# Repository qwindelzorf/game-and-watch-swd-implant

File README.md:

# Game & Watch SWD-Implant

A small [DAP-Link](https://github.com/ARMmbed/DAPLink) SWD programmer/debugger that fits insight a Nintendo® Game & Watch™ (2020/2021).

This is forked from [UlfWetzker/game-and-watch-swd-implant](https://github.com/UlfWetzker/game-and-watch-swd-implant), which has some issues and appears to be unmaintained.

## Mario (2020)

## Zelda (2021)

## Implant Firmware

The implant board itself uses a [SAMD21](https://www.microchip.com/en-us/product/atsamd21g18) microcontroller, which is flashed with the [DAP-Link](https://github.com/ARMmbed/DAPLink) firmware. It is then able to act as a flasher for the G&W [STM32](https://www.st.com/en/microcontrollers-microprocessors/stm32-32-bit-arm-cortex-mcus.html) CPU. Flashing both the implant and the G&W is done using [OpenOCD](https://openocd.org/).

## G&W Firmware

The go-to firmware for these consoles is "RetroGo":
- [Original](https://github.com/kbeckmann/game-and-watch-retro-go): archived now
- [Zeus Fork](https://github.com/olderzeus/game-and-watch-retro-go): Adds more consoles
- [Sylverb Fork](https://github.com/sylverb/game-and-watch-retro-go): Adds yet more consoles, as well as support for LttP and SMW.

## Other Links

- SD Card mod: [link](https://github.com/sylverb/game-and-watch-retro-go-sd)
- Original homebrew work: [link](https://github.com/ghidraninja/game-and-watch-backup)
- Various firmware and utilities: [link](https://www.schuerewegen.tk/gnw/)
- A good tutorial on modding & flashing: [link](https://psxtools.de/forum/index.php?thread/87820-tutorial-zelda-mario-game-and-watch-64mb-upgrade-dualboot-ofw-retro-go/) (German)

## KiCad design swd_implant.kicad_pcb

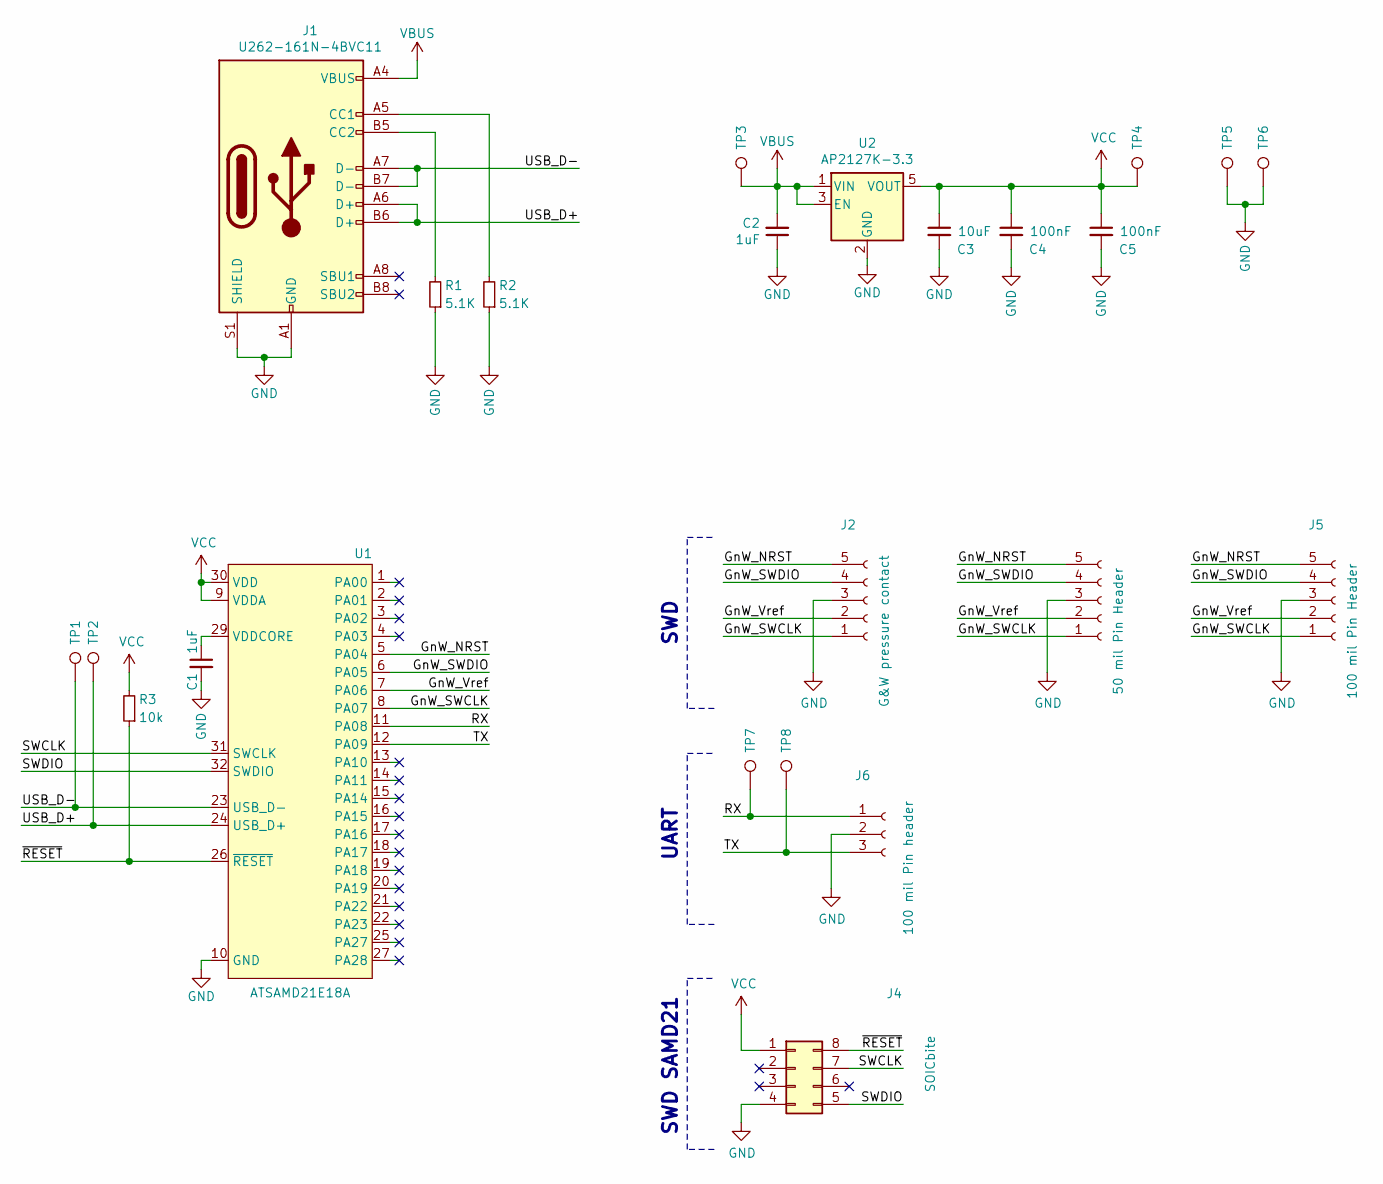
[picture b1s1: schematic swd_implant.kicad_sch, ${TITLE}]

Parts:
C1, C2: 1uF; C_0402_1005Metric; MFR.Part # CL05A105KA5NQNC; LCSC Part # C52923
C3: 10uF; C_0402_1005Metric; MFR.Part # CL05A106MQ5NUNC; LCSC Part # C15525
C4, C5: 100nF; C_0402_1005Metric; MFR.Part # CL05B104KO5NNNC; LCSC Part # C1525
J1: U262-161N-4BVC11; USB_C_Receptacle_XKB_U262-16XN-4BVC11; Mfr.Part # U262-161N-4BVC11; LCSC Part # C319148
J2: G&W pressure contact; GnW_SWD
J3: 50 mil Pin Header; PinHeader_1x05_P1.27mm_Vertical
J4: SOICbite; SOIC_clipProgSmall
J5: 100 mil Pin Header; PinHeader_1x05_P2.45mm_edge
J6: 100 mil Pin header; PinHeader_1x03_P2.45mm_edge
R1, R2: 5.1K; R_0402_1005Metric; MFR.Part # 0402WGF5101TCE; LCSC Part # C25905
R3: 10k; R_0402_1005Metric; MFR.Part # 0402WGJ0103TCE; LCSC Part # C25531
TP1, TP3, TP4, TP5, TP6, TP7, TP8: TP_USB_D+; TestPoint_Pad_D1.0mm
TP2: TP_USB_D-; TestPoint_Pad_D1.0mm
U1: ATSAMD21E18A; QFN-32-1EP_5x5mm_P0.5mm_EP3.6x3.6mm; MFR.Part # ATSAMD21E18A-MU; LCSC Part # C220692
U2: AP2127K-3.3; SOT-23-5; MFR.Part # AP2127K-3.3TRG1; LCSC Part # C156285

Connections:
/GnW_NRST: J2.5, J3.5, J5.5, U1.5 (PA04)
/GnW_SWCLK: J2.1, J3.1, J5.1, U1.8 (PA07)
/GnW_SWDIO: J2.4, J3.4, J5.4, U1.6 (PA05)
/GnW_Vref: J2.2, J3.2, J5.2, U1.7 (PA06)
/RX: J6.1, TP7.1, U1.11 (PA08)
/SWCLK: J4.7, U1.31 (SWCLK)
/SWDIO: J4.5, U1.32 (SWDIO)
/TX: J6.3, TP8.1, U1.12 (PA09)
/USB_D+: J1.A6 (D+), J1.B6 (D+), TP2.1, U1.24 (USB_D+)
/USB_D-: J1.A7 (D-), J1.B7 (D-), TP1.1, U1.23 (USB_D-)
/~RESET: J4.8, R3.1, U1.26 (~RESET)
GND: C1.2, C2.1, C3.2, C4.2, C5.2, J1.A1 (GND), J1.A12 (GND), J1.B1 (GND), J1.B12 (GND), J1.S1 (SHIELD), J2.3, J2.6, J2.7, J3.3, J4.4, J5.3, J6.2, R1.1, R2.1, TP5.1, TP6.1, U1.10 (GND), U1.28 (GND), U1.33, U2.2 (GND)
unnamed: J1.A5 (CC1), R2.2
unnamed: J1.B5 (CC2), R1.2
unnamed: C1.1, U1.29 (VDDCORE)
VBUS: C2.2, J1.A4 (VBUS), J1.A9 (VBUS), J1.B4 (VBUS), J1.B9 (VBUS), TP3.1, U2.1 (VIN), U2.3 (EN)
VCC: C3.1, C4.1, C5.1, J4.1, R3.2, TP4.1, U1.9 (VDDA), U1.30 (VDD), U2.5 (VOUT)

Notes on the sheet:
UART
SWD SAMD21
SWD

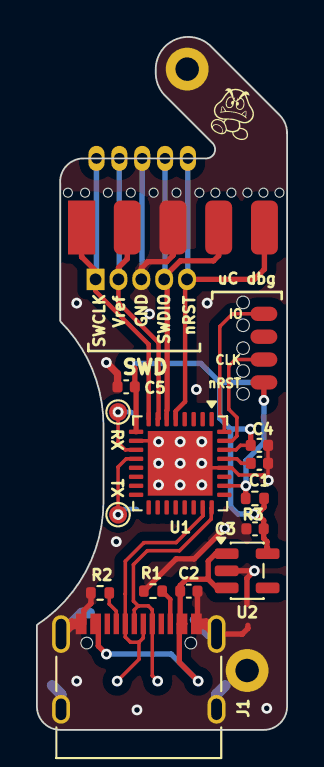
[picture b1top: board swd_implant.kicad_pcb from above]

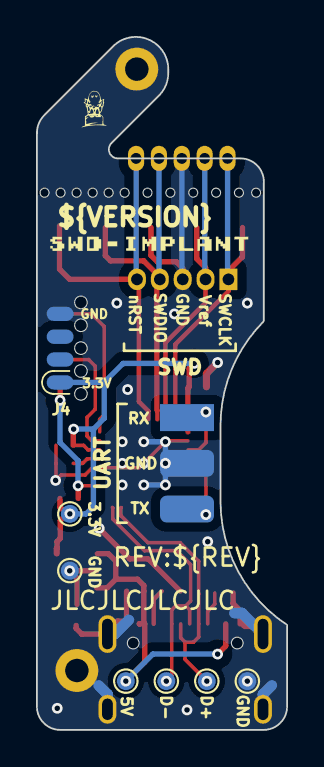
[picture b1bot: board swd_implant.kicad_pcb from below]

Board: 2 copper layers, 13.9 x 38.5 mm, 26 parts (10 on the bottom side), 17 nets.

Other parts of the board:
Q**: Qwindelzorf; qwindelzorf_1520
Ref**: Val**; name_logo

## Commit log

2025-10-25 Ignore more temp files
2025-10-25 New board outline & swd pinout fixes
    Changed the board outline to work with castellated edges, making it possible to
    solder down instead of just relying on pressure contact.
    Also fixed the inverted SWD pinout from upstream.
2025-10-25 Update readme
    Adding useful links, and updating images
2025-10-25 Fix image layout
2025-10-25 Add M marker to front of board
    This M is to indicate that it is the "Mario" variant of the implant
    board.
2025-10-25 Add Z marker to front of board
    This Z is to indicate that it is the "Zelda" variant of the implant
    board.
2025-10-25 Add Zelda version of implant
    Just changed the board shape to fit the altered location of the SWD pins
    on that version.
2025-10-25 Prep for fabrication
2025-10-26 more fabrication updates
2025-10-26 Add LCSC part numbers
2025-10-27 Add logos
